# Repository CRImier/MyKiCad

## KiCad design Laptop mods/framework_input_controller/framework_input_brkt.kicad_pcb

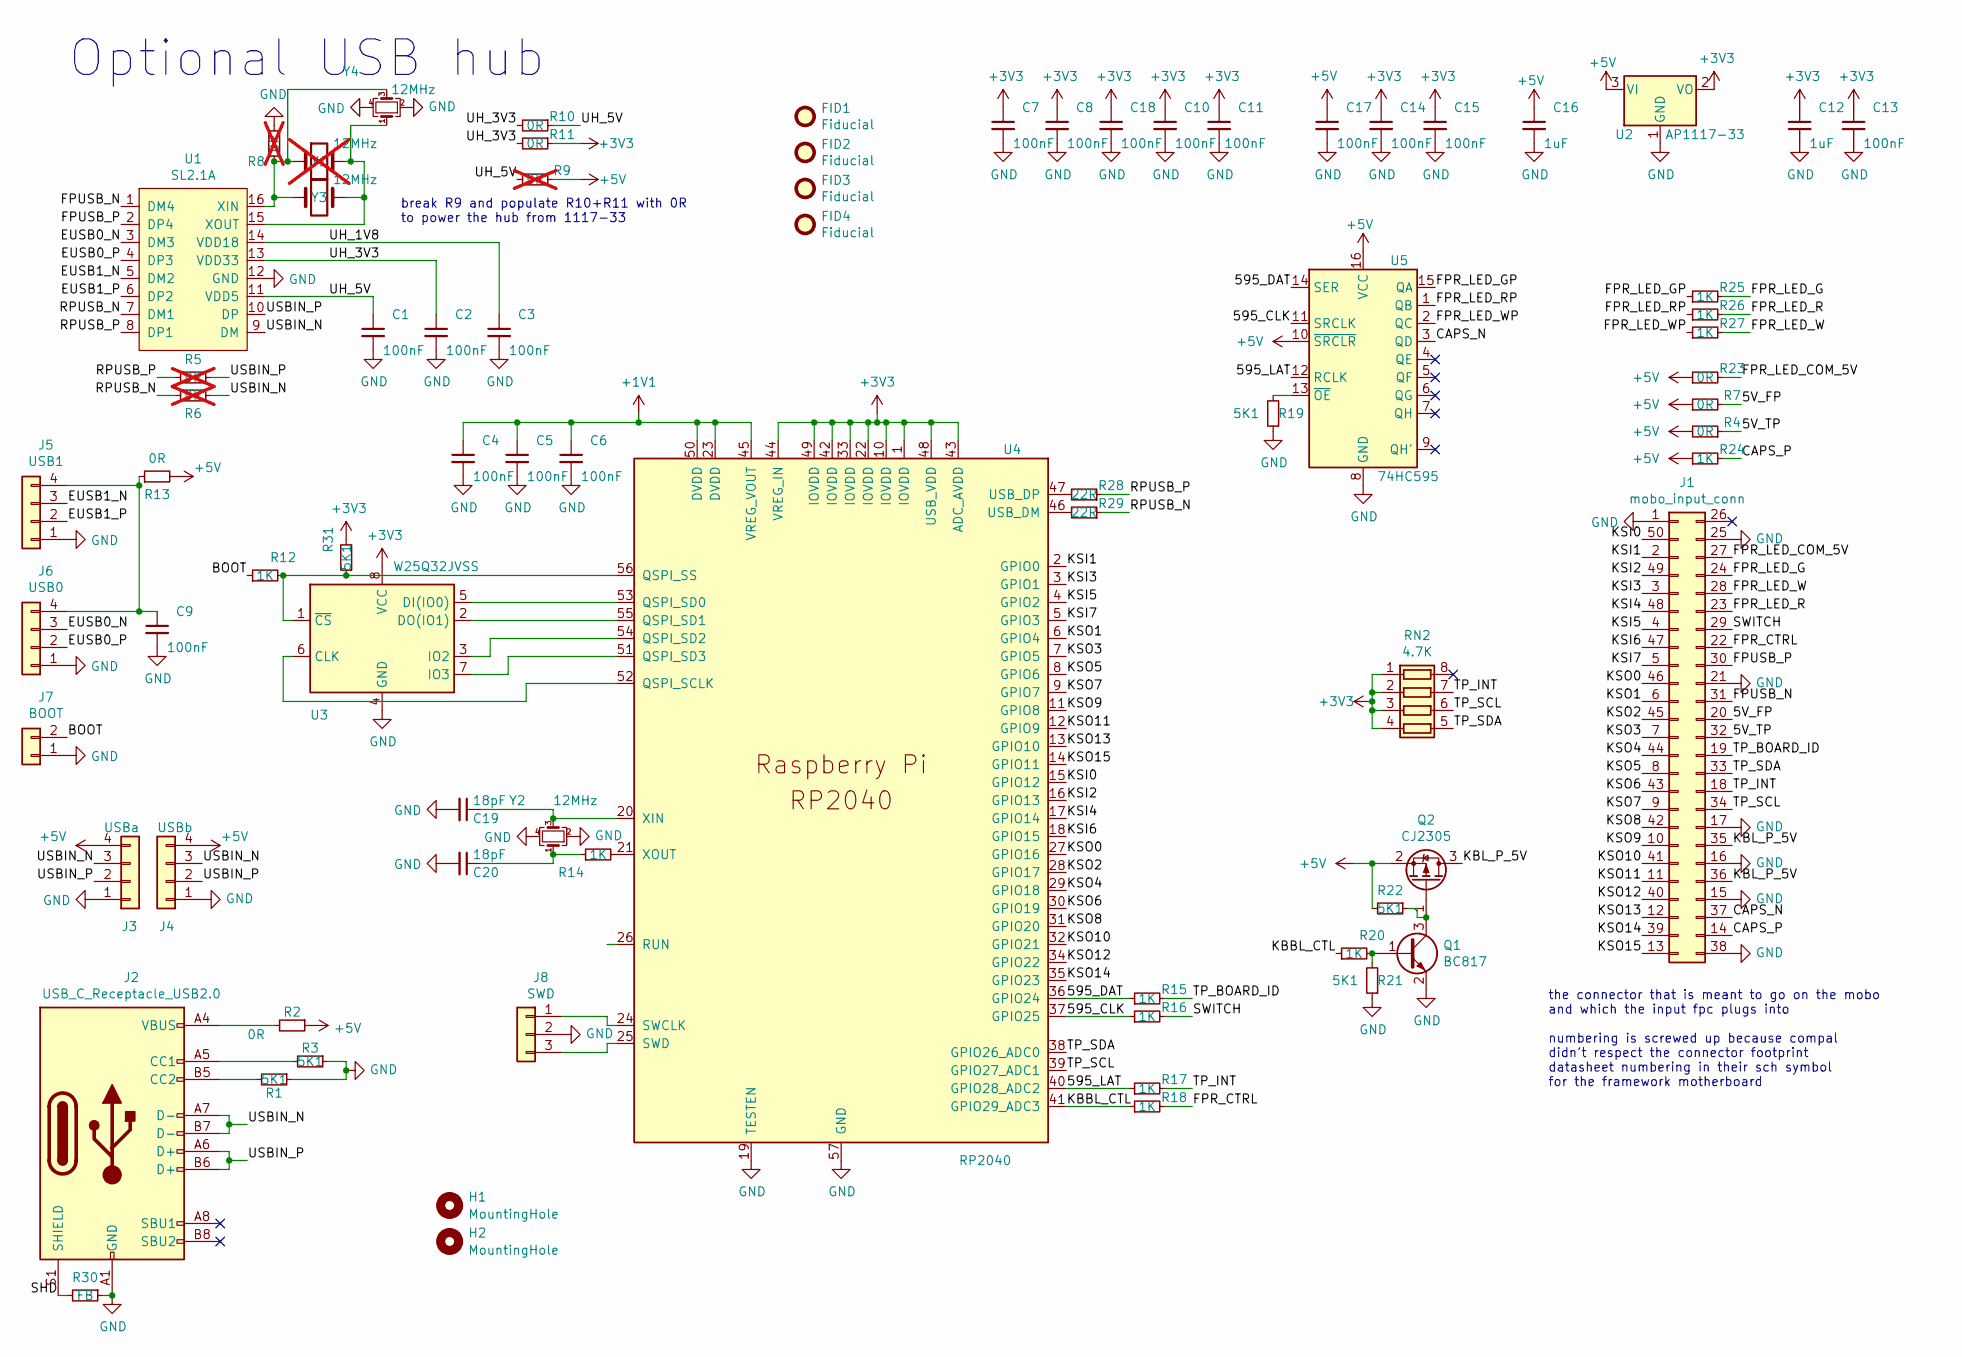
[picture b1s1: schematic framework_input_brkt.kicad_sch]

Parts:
C1, C2, C3, C4, C5, C7, C8, C9, C10, C11, C13, C14, C15, C17, C18: 100nF; C_0603_1608Metric
C6: 100nF; R_0603_1608Metric
C12, C16: 1uF; C_0603_1608Metric
C19, C20: 18pF; C_0603_1608Metric
FID1, FID2, FID3, FID4: Fiducial; Fiducial_1mm_Mask2mm
H1, H2: MountingHole; MountingHole_3mm
J1: mobo_input_conn; Amphenol_10156000
J2: USB_C_Receptacle_USB2.0; USB_C_Receptacle_HRO_TYPE-C-31-M-12
J3: USBa; PinHeader_1x04_P2.54mm_Vertical
J4: USBb; PinHeader_1x04_P2.54mm_Vertical
J5: USB1; PinHeader_1x04_P2.54mm_Vertical
J6: USB0; PinHeader_1x04_P2.54mm_Vertical
J7: BOOT; PinHeader_1x02_P2.54mm_Vertical
J8: SWD; PinHeader_1x03_P2.54mm_Vertical
Q1: BC817; SOT-23
Q2: CJ2305; SOT-23
R1, R3, R19, R21, R22, R31: 5K1; R_0603_1608Metric
R2, R13: 0R; R_0805_2012Metric
R4, R7, R10, R11, R23: 0R; R_0603_1608Metric
R5, R6, R8, R9: 0R; R_0603_1608Metric; not fitted
R12, R14, R15, R16, R17, R18, R20, R24, R25, R26, R27: 1K; R_0603_1608Metric
R28, R29: 22R; R_0402_1005Metric
R30: FB; R_0805_2012Metric
RN2: 4.7K; R_Array_Concave_4x0603
U1: SL2.1A; SO-16_3.9x9.9mm_P1.27mm
U2: AP1117-33; SOT-223-3_TabPin2
U3: W25Q32JVSS; SOIC-8_5.23x5.23mm_P1.27mm
U4: RP2040; RP2040-QFN-56
U5: 74HC595; SO-16_3.9x9.9mm_P1.27mm
Y1: 12MHz; Crystal_HC49-U_Vertical; not fitted
Y2, Y4: 12MHz; Crystal_SMD_3225-4Pin_3.2x2.5mm
Y3: 12MHz; Crystal_SMD_HC49-SD

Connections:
+1V1: C4.1, C5.1, C6.1, U4.23 (DVDD), U4.45 (VREG_VOUT), U4.50 (DVDD)
+3V3: C7.1, C8.1, C10.1, C11.1, C12.1, C13.1, C14.1, C15.1, C18.1, R11.1, R31.2, RN2.1 (R1.1), RN2.2 (R2.1), RN2.3 (R3.1), RN2.4 (R4.1), U2.2 (VO), U3.8 (VCC), U4.1 (IOVDD), U4.10 (IOVDD), U4.22 (IOVDD), U4.33 (IOVDD), U4.42 (IOVDD), U4.43 (ADC_AVDD), U4.44 (VREG_IN), U4.48 (USB_VDD), U4.49 (IOVDD)
+5V: C16.1, C17.1, J3.4, J4.4, Q2.2 (S), R2.1, R4.2, R7.1, R9.1, R13.2, R22.2, R23.1, R24.1, U2.3 (VI), U5.10 (~SRCLR), U5.16 (VCC)
/5V_FP: J1.20, R7.2
/5V_TP: J1.32, R4.1
/595_CLK: R16.1, U4.37 (GPIO25), U5.11 (SRCLK)
/595_DAT: R15.1, U4.36 (GPIO24), U5.14 (SER)
/595_LAT: R17.1, U4.40 (GPIO28_ADC2), U5.12 (RCLK)
/BOOT: J7.2, R12.1
/CAPS_N: J1.37, U5.3 (QD)
/CAPS_P: J1.14, R24.2
/EUSB0_N: J6.3, U1.3 (DM3)
/EUSB0_P: J6.2, U1.4 (DP3)
/EUSB1_N: J5.3, U1.5 (DM2)
/EUSB1_P: J5.2, U1.6 (DP2)
/FPR_CTRL: J1.22, R18.2
/FPR_LED_COM_5V: J1.27, R23.2
/FPR_LED_G: J1.24, R25.2
/FPR_LED_GP: R25.1, U5.15 (QA)
/FPR_LED_R: J1.23, R26.2
/FPR_LED_RP: R26.1, U5.1 (QB)
/FPR_LED_W: J1.28, R27.2
/FPR_LED_WP: R27.1, U5.2 (QC)
/FPUSB_N: J1.31, U1.1 (DM4)
/FPUSB_P: J1.30, U1.2 (DP4)
/KBBL_CTL: R18.1, R20.1, U4.41 (GPIO29_ADC3)
/KBL_P_5V: J1.35, J1.36, Q2.3 (D)
/KSI0: J1.50, U4.15 (GPIO12)
/KSI1: J1.2, U4.2 (GPIO0)
/KSI2: J1.49, U4.16 (GPIO13)
/KSI3: J1.3, U4.3 (GPIO1)
/KSI4: J1.48, U4.17 (GPIO14)
/KSI5: J1.4, U4.4 (GPIO2)
/KSI6: J1.47, U4.18 (GPIO15)
/KSI7: J1.5, U4.5 (GPIO3)
/KSO0: J1.46, U4.27 (GPIO16)
/KSO1: J1.6, U4.6 (GPIO4)
/KSO2: J1.45, U4.28 (GPIO17)
/KSO3: J1.7, U4.7 (GPIO5)
/KSO4: J1.44, U4.29 (GPIO18)
/KSO5: J1.8, U4.8 (GPIO6)
/KSO6: J1.43, U4.30 (GPIO19)
/KSO7: J1.9, U4.9 (GPIO7)
/KSO8: J1.42, U4.31 (GPIO20)
/KSO9: J1.10, U4.11 (GPIO8)
/KSO10: J1.41, U4.32 (GPIO21)
/KSO11: J1.11, U4.12 (GPIO9)
/KSO12: J1.40, U4.34 (GPIO22)
/KSO13: J1.12, U4.13 (GPIO10)
/KSO14: J1.39, U4.35 (GPIO23)
/KSO15: J1.13, U4.14 (GPIO11)
/RPUSB_N: R6.1, R29.1, U1.7 (DM1)
/RPUSB_P: R5.1, R28.1, U1.8 (DP1)
/SHD: J2.S1 (SHIELD), R30.2
/SWITCH: J1.29, R16.2
/TP_BOARD_ID: J1.19, R15.2
/TP_INT: J1.18, R17.2, RN2.7 (R2.2)
/TP_SCL: J1.34, RN2.6 (R3.2), U4.39 (GPIO27_ADC1)
/TP_SDA: J1.33, RN2.5 (R4.2), U4.38 (GPIO26_ADC0)
/UH_1V8: C3.1, U1.14 (VDD18)
/UH_3V3: C2.1, R10.2, R11.2, U1.13 (VDD33)
/UH_5V: C1.1, R9.2, R10.1, U1.11 (VDD5)
/USBIN_N: J2.A7 (D-), J2.B7 (D-), J3.3, J4.3, R6.2, U1.9 (DM)
/USBIN_P: J2.A6 (D+), J2.B6 (D+), J3.2, J4.2, R5.2, U1.10 (DP)
GND: C1.2, C2.2, C3.2, C4.2, C5.2, C6.2, C7.2, C8.2, C9.2, C10.2, C11.2, C12.2, C13.2, C14.2, C15.2, C16.2, C17.2, C18.2, C19.2, C20.2, J1.1, J1.15, J1.16, J1.17, J1.21, J1.25, J1.38, J2.A1 (GND), J2.A12 (GND), J2.B1 (GND), J2.B12 (GND), J3.1, J4.1, J5.1, J6.1, J7.1, J8.2, Q1.2 (E), R1.1, R3.1, R8.2, R19.1, R21.1, R30.1, U1.12 (GND), U2.1 (GND), U3.4 (GND), U4.19 (TESTEN), U4.57 (GND), U5.8 (GND), Y2.2, Y2.4, Y4.2, Y4.4
unnamed: C20.1, R14.1, Y2.1
unnamed: J2.A5 (CC1), R3.2
unnamed: J2.B5 (CC2), R1.2
unnamed: J2.A4 (VBUS), J2.A9 (VBUS), J2.B4 (VBUS), J2.B9 (VBUS), R2.2
unnamed: C9.1, J5.4, J6.4, R13.1
unnamed: J8.1, U4.24 (SWCLK)
unnamed: J8.3, U4.25 (SWD)
unnamed: Q1.1 (B), R20.2, R21.2
unnamed: Q1.3 (C), Q2.1 (G), R22.1
unnamed: R8.1, U1.16 (XIN), Y1.1, Y3.1, Y4.3
unnamed: U1.15 (XOUT), Y1.2, Y3.2, Y4.1
unnamed: U3.6 (CLK), U4.52 (QSPI_SCLK)
unnamed: U3.5 (DI(IO0)), U4.53 (QSPI_SD0)
unnamed: U3.2 (DO(IO1)), U4.55 (QSPI_SD1)
unnamed: U3.3 (IO2), U4.54 (QSPI_SD2)
unnamed: U3.7 (IO3), U4.51 (QSPI_SD3)
unnamed: R12.2, R31.1, U3.1 (~CS), U4.56 (QSPI_SS)
unnamed: R29.2, U4.46 (USB_DM)
unnamed: R28.2, U4.47 (USB_DP)
unnamed: C19.1, U4.20 (XIN), Y2.3
unnamed: R14.2, U4.21 (XOUT)
unnamed: R19.2, U5.13 (~OE)

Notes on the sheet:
Optional USB hub
the connector that is meant to go on the mobo and which the input fpc plugs into numbering is screwed up because compal didn't respect the connector footprint datasheet numbering in their sch symbol for the framework motherboard
break R9 and populate R10+R11 with 0R to power the hub from 1117-33

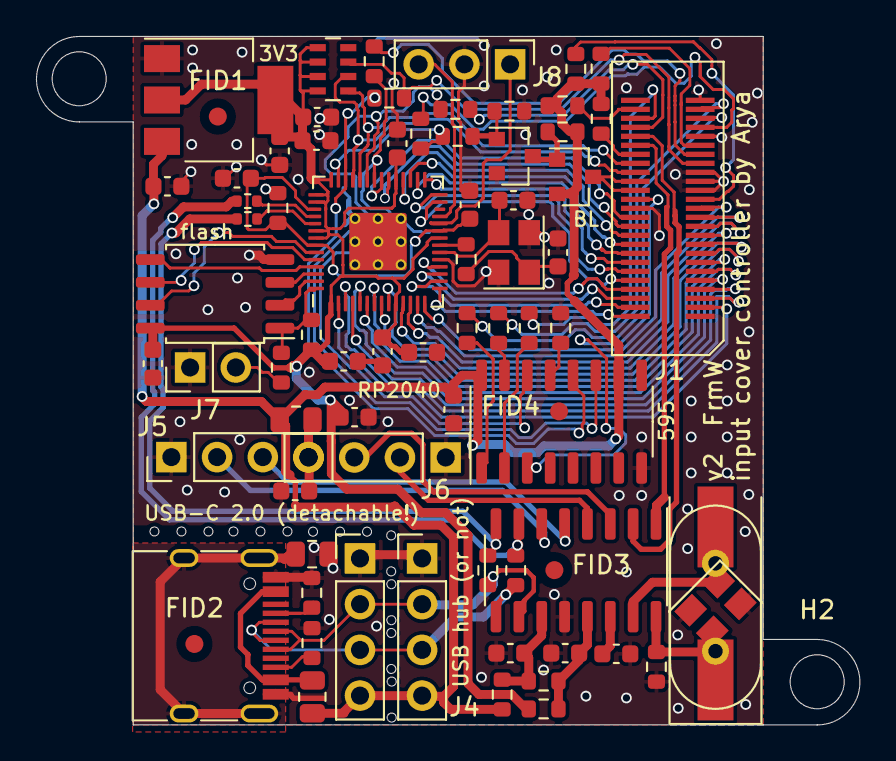
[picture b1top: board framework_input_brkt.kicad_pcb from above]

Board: 2 copper layers, 45.8 x 38.2 mm, 77 parts (0 on the bottom side), 87 nets.

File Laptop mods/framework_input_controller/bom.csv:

Designator,Footprint,Quantity,Value,LCSC Part #
"C1, C10, C11, C13, C14, C15, C17, C18, C2, C3, C4, C5, C6, C7, C8, C9",0603,16,100nF,C14663
"C12, C16",0603,2,1uF,C15849
"C19, C20",0603,2,18pF,C1647
"FID1, FID2, FID3, FID4",Fiducial_1mm_Mask2mm,4,Fiducial,
J1,Amphenol_10156000,1,mobo_input_conn,
J2,USB_C_Receptacle_HRO_TYPE-C-31-M-12,1,USB_C_Receptacle_USB2.0,C2874568
Q1,SOT-23,1,BC817,C2137
Q2,SOT-23,1,CJ2305,C8549
"R1, R19, R21, R22, R3, R31",0603,5,5K1,C23186
"R10, R11, R23, R4, R5, R6, R7, R8, R9",0603,9,0R,C21189
"R12, R14, R15, R16, R17, R18, R20, R24, R25, R26, R27",0603,11,1K,C21190
"R13, R2",0805,2,0R,C17477
R30,0805,1,FB,C1011
"R28, R29",0402,2,22R,C25092
RN2,R_Array_Concave_4x0603,1,4.7K,C1980
U1,SO-16_3.9x9.9mm_P1.27mm,1,SL2.1A,C192893
U2,SOT-223-3_TabPin2,1,AP1117-33,C5400
U3,SOIC-8_5.23x5.23mm_P1.27mm,1,W25Q32JVSS,C179173
U4,RP2040-QFN-56,1,RP2040,C2040
U5,SO-16_3.9x9.9mm_P1.27mm,1,74HC595,C2927048
Y1,Crystal_HC49-U_Vertical,1,12MHz,
Y2,Crystal_SMD_3225-4Pin_3.2x2.5mm,1,12MHz,C258938
Y3,Crystal_SMD_HC49-SD,1,12MHz,C108151

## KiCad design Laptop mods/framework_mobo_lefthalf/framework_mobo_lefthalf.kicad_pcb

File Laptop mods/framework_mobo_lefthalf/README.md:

# Framework Display Shim

This is a start for reimplementing the Framework Mainboard.
Currently, this board is a USB-C DP altmode to Framework display adapter,
using the same connector and pinout that the Framework mainboard uses.

This adapter is currently going through the testing process, with a number of fundamental fixes scheduled for the v3 version.

## Images

## Notes

- This board is untested and there's no guarantees of fitness.
- I recommend a stencil for assembling this board.

## Info

- Software: Kicad 7
- Version: 2
- PCB size: w*h
- Layer count: 6
- Recommended thickness: 0.8mm/1mm (needs to match Framework mainboard thickness)

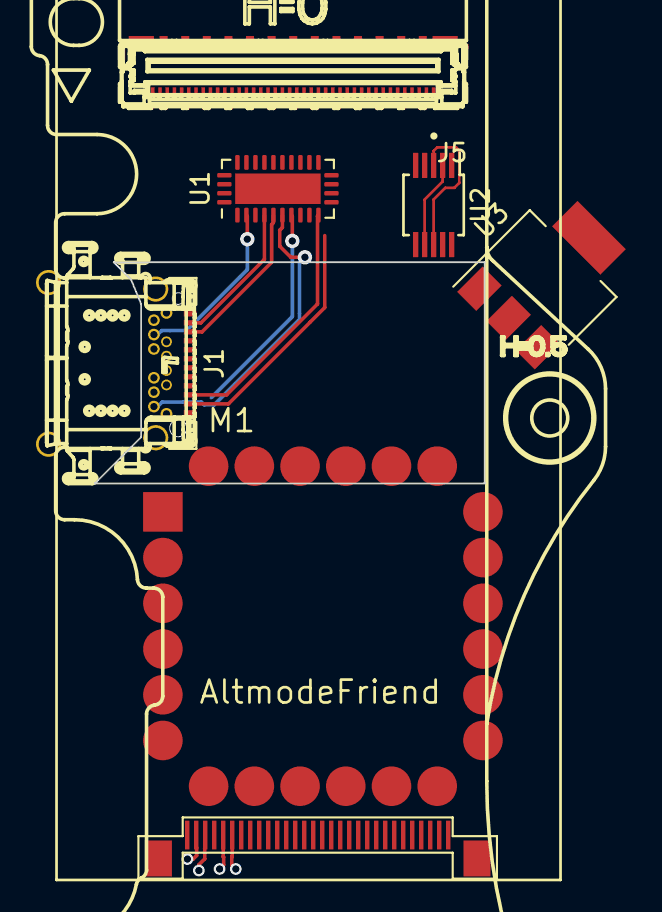
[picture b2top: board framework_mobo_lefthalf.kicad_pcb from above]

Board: 6 copper layers, 7 parts (0 on the bottom side), 39 nets.

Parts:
J1: USB_C_Receptacle; USB_C_Receptacle_Amphenol_12401548E4-2A_CircularHoles
J2: IF; FPC_30
J5: Display; IPEX_20879-040E-01
M1: AltmodeFriend; altmode_friend
U1: VL170; QFN-28-1EP_3x6mm_P0.5mm_EP1.7x4.75mm
U2: FSUSB30MUX; MSOP-10_3x3mm_P0.5mm
U3: AP1117-33; SOT-223-3_TabPin2

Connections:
3V_TS: J5.29, J5.30
+3.3V: J2.13, J2.14, J2.15, M1.8 (3V3), U3.2 (VO)
+3.3VP: U1.22 (VCC), U2.10 (VCC)
/3VP_CTL: J2.9, M1.13 (GP7)
/CC1: J1.A5 (CC1), M1.20 (CC1)
/CC2: J1.B5 (CC2), M1.22 (CC2)
/PD_D+: J2.3, M1.24 (D+)
/PD_D-: J2.2, M1.23 (D-)
/PD_UART_RX: J2.12, M1.5 (GP1)
/PD_UART_TX: J2.11, M1.4 (GP0)
/SBU_OE: M1.11 (GP5), U2.9 (~OE)
/SBU_S: M1.12 (GP6), U2.1 (S)
/TC1_CSBU1: J1.A8 (SBU1), U1.11 (CSBU1)
/TC1_CSBU2: J1.B8 (SBU2), U1.12 (CSBU2)
/TC1_RX1+: J1.B11 (RX1+), U1.1 (RX1_P)
/TC1_RX1-: J1.B10 (RX1-), U1.2 (RX1_N)
/TC1_RX2+: J1.A11 (RX2+), U1.9 (RX2_P)
/TC1_RX2-: J1.A10 (RX2-), U1.10 (RX2_N)
/TC1_SBU1: U1.13 (SBU1), U2.4 (D+)
/TC1_SBU2: U1.14 (SBU2), U2.6 (D-)
/TC1_TX1+: J1.A2 (TX1+), U1.4 (TX1_P)
/TC1_TX1-: J1.A3 (TX1-), U1.5 (TX1_N)
/TC1_TX2+: J1.B2 (TX2+), U1.6 (TX2_P)
/TC1_TX2-: J1.B3 (TX2-), U1.7 (TX2_N)
/TC_D+: J1.A6 (D+), J1.B6 (D+), J2.6
/TC_D-: J1.A7 (D-), J1.B7 (D-), J2.5
/VL170_AMSEL: M1.7 (GP3), U1.8 (AMSEL)
/VL170_EN: M1.6 (GP2), U1.17 (EN)
/VL170_POL: M1.10 (GP4), U1.3 (POL)
AUX+: U2.3 (HSD2+), U2.8 (HSD1-)
AUX-: U2.2 (HSD1+), U2.7 (HSD2-)
BLK_OFF_N: J5.23, M1.16 (GP10)
BLK_PWM_LCD: J5.22, M1.17 (GP15)
BL_POWER: J5.1, J5.2, J5.3
BL_PWR_IN: J2.18, J2.19
DPHPD: J5.21, M1.18 (GP17)
GND: J1.A1 (GND), J1.A12 (GND), J1.B1 (GND), J1.B12 (GND), J1.S1 (SHIELD), J2.1, J2.4, J2.7, J2.10, J2.16, J2.17, J2.20, J2.21, J2.22, J2.23, J2.24, J2.MP (MountPin), J5.5, J5.8, J5.11, J5.14, J5.17, J5.20, J5.39, J5.40, M1.9 (GND), M1.19 (GND), U1.29 (GND), U2.5 (GND), U3.1 (GND)
unnamed: J5.26, J5.27, J5.28
VBUS: J1.A4 (VBUS), J1.A9 (VBUS), J1.B4 (VBUS), J1.B9 (VBUS), J2.25, J2.26, J2.27, J2.28, J2.29, J2.30, U3.3 (VI)

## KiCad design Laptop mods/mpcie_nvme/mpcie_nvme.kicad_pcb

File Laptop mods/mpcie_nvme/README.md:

# mPCIe-NVMe adapter

This is an adapter to easily connect NVMe drives to systems with
mPCIe slots. It will support M.2 M-key and M+B-key drives.
It's a half-height card, if you'd like to put it in a full-height slot,
you'll need a mechanical adapter of some kind.

There are traces with mask openings near the mPCIe card edge that allow you
to tap into any of the mPCIe socket pins connected to the card's pads (except the PCI-E pins).
Use them wisely!

This board is untested and there's no guarantees of fitness.

- PCB size: 30x26.8mm
- Layer count: 2
- Recommended thickness: 1mm (won't fit in an mPCIe slot otherwise)

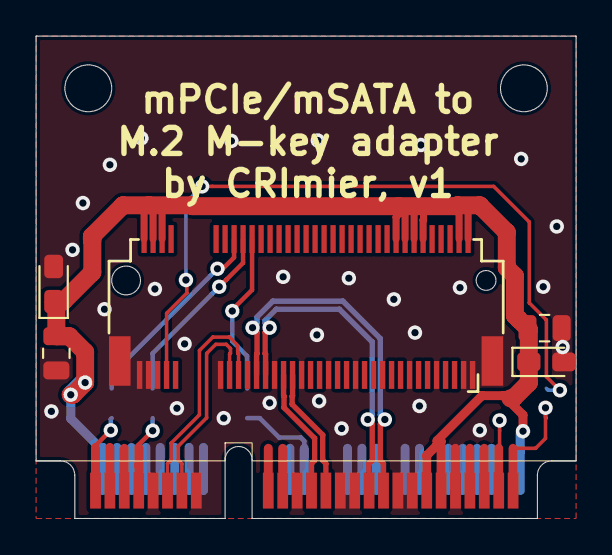
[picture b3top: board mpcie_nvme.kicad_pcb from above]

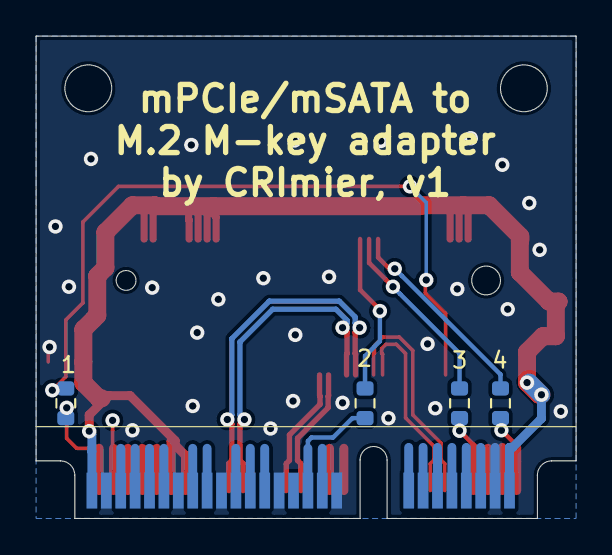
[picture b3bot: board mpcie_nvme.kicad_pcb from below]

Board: 2 copper layers, 30.0 x 26.8 mm, 10 parts (4 on the bottom side), 16 nets.

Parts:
C1, C3: 100nF; C_0805_2012Metric
C2, C4: 100uF; CP_EIA-2012-12_Kemet-R_Pad1.30x1.05mm_HandSolder
R1, R2, R3, R5: 0R; R_0603_1608Metric
U1: MPCIE-Socket; mpcie-half-card
U2: NGFF_M; Conn_TE-M.2-0.5-67P-doublesided_TypeM

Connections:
+3V3: C1.1, C2.1, C3.1, C4.1, U1.2, U1.24, U1.39, U1.41, U1.52, U2.2, U2.4, U2.12, U2.14, U2.16, U2.18, U2.70, U2.72, U2.74
DET: R5.1, U2.69
GND: C1.2, C2.2, C3.2, C4.2, U1.4, U1.9, U1.15, U1.18, U1.21, U1.26, U1.27, U1.29, U1.34, U1.35, U1.37, U1.40, U1.43, U1.50, U2.1, U2.3, U2.9, U2.15, U2.21, U2.27, U2.33, U2.39, U2.45, U2.51, U2.57, U2.71, U2.73, U2.75, U2.MP
unnamed: R1.1, U1.22
unnamed: R2.2, U1.1
unnamed: R3.2, U1.7
unnamed: R5.2, U1.51
P0_RX+: U1.25, U2.41
P0_RX-: U1.23, U2.43
P0_TX+: U1.31, U2.47
P0_TX-: U1.33, U2.49
PCLK+: U1.13, U2.55
PCLK-: U1.11, U2.53
PERST: R1.2, U2.50
~CLKREQ: R3.1, U2.52
~WAKE: R2.1, U2.54

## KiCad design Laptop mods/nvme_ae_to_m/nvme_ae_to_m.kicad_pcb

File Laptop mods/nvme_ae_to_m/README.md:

# M.2 A+E to M key adapter

This board allows you to insert M-key M.2 SSDs into A/E-key slots.
It should support NVMe SSDs at 1x speed. It might even support SATA if the PCI-E lane
going to the slot is PCI-E/SATA and you can figure out a way to switch it
into SATA mode, but that doesn't happen all that often.

M.2 socket position is calculated so that the board
mechanically converts a 2230 card into a 2242 card - that's not terribly useful
since most WiFi cards I see are 2230 already, I just didn't see any sense
in changing the position. The board itself is 2230.
FOXCONN AS0BC21-S20BM-7H socket datasheet was used for reference.

This board also breaks out A+E slot USB 2.0 signals, 3.3V and GND
on a separate 4-pin 2mm pin header. It's mostly intended for you
to solder wires to. Draw 3.3V from there at your own peril.

There are resistors on the bottom for interrupting PCI-E&other control signals
if any of them interfere with operation of your SSD:

* 1 interrupts PERST
* 2 interrupts CLKREQ
* 3 interrupts PEWAKE
* 4 interrupts SUSCLK

There are also traces with mask openings near the card edge that allow you
to tap into any of the M.2 socket pins connected to the A+E pads. Use them wisely!

USB header pinout is silkscreened on the board's bottom layer.

Changes in v2:

- Removed capacitors
- v1 had TX and RX pairs swapped, fixed in new revision

- Software: Kicad 6
- Version: 2
- PCB size: 22*16,42
- Layer count: 2
- Recommended thickness: 0.8mm (M.2 card thickness)

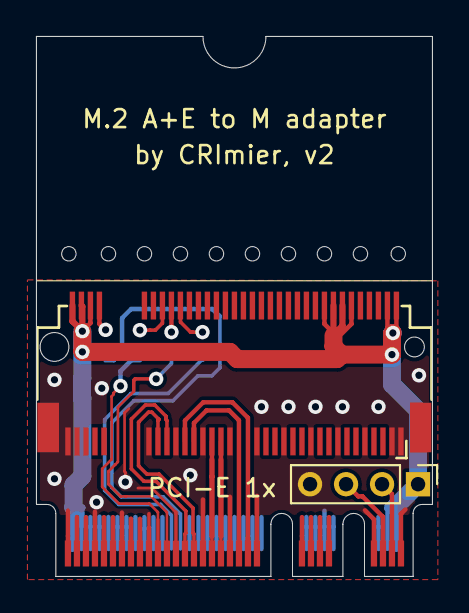
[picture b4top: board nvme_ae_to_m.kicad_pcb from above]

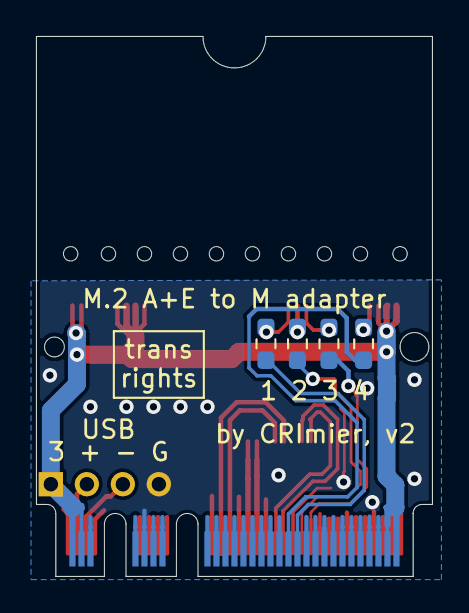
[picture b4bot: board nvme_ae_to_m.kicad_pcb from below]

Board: 2 copper layers, 22.0 x 30.0 mm, 7 parts (4 on the bottom side), 18 nets.

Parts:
J1: USB; PinHeader_1x04_P2.00mm_Vertical
R1, R2, R3, R4: 0R; R_0603_1608Metric_Pad0.98x0.95mm_HandSolder
U1: NGFF_M; Conn_TE-M.2-0.5-67P-doublesided_TypeM
U2: NGFF_AE; NGFF_A+E

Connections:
+3V3: J1.1, U1.2, U1.4, U1.12, U1.14, U1.16, U1.18, U1.70, U1.72, U1.74, U2.2, U2.4, U2.72, U2.74
/PER0+: U1.49, U2.35
/PER0-: U1.47, U2.37
/PET0+: U1.41, U2.41
/PET0-: U1.43, U2.43
/REFCLK+: U1.55, U2.47
/REFCLK-: U1.53, U2.49
D+: J1.2, U2.3
D-: J1.3, U2.5
GND: J1.4, U1.1, U1.3, U1.9, U1.15, U1.21, U1.27, U1.33, U1.39, U1.45, U1.51, U1.57, U1.71, U1.73, U1.75, U1.MP, U2.1, U2.7, U2.18, U2.33, U2.39, U2.45, U2.51, U2.57, U2.63, U2.69, U2.75
unnamed: R1.1, U2.53
unnamed: R2.1, U2.55
unnamed: R3.2, U2.52
unnamed: R4.2, U2.50
SUSCLK: R4.1, U1.68
~CLKREQ: R1.2, U1.52
~PERST: R3.1, U1.50
~PEWAKE: R2.2, U1.54

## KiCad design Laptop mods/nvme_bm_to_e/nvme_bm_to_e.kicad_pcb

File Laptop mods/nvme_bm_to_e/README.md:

# M.2 B+M to E key adapter

This board allows you to insert E-key or A+E-key WiFi cards into B-key or M-key slots.
It should support PCIe WiFi cards and passes the USB channel through.
It won't support CNVi cards.

M.2 socket position is calculated so that the board
mechanically converts a 2230 card into a 2242 card -
which is perfect for WiFi cards in 2242-oriented B-key slots.
FOXCONN AS0BC21-S20BM-7H socket datasheet was used for reference.

This board also breaks out USB 2.0 signals and GND
on a separate 4-pin 2mm pin header. It's mostly intended for you
to solder wires to, in case you're 
If inserting into M.2 socket, you might have to mask USB pins on the card edge side
with kapton tape.

There are resistors on the bottom for interrupting PCI-E&other control signals
if any of them interfere with operation of your WiFi card:

* 1 interrupts SUSCLK
* 2 connects B-key W_DISABLE to E-key W_DIS2
* 3 connects B-key W_DISABLE to E-key W_DIS1
* 4 interrupts PERST
* 5 interrupts PEWAKE
* 6 interrupts CLKREQ

You can snap part of this board off if you need to save space.
There are also traces with mask openings near the card edge that allow you
to tap into any of the M.2 socket pins connected to the B+M pads. Use them wisely!

USB header pinout is silkscreened on the board's bottom layer.
This board is untested and there's no guarantees of fitness.

- PCB size: 22*42mm
- Layer count: 2
- Recommended thickness: 0.8mm (M.2 card thickness)

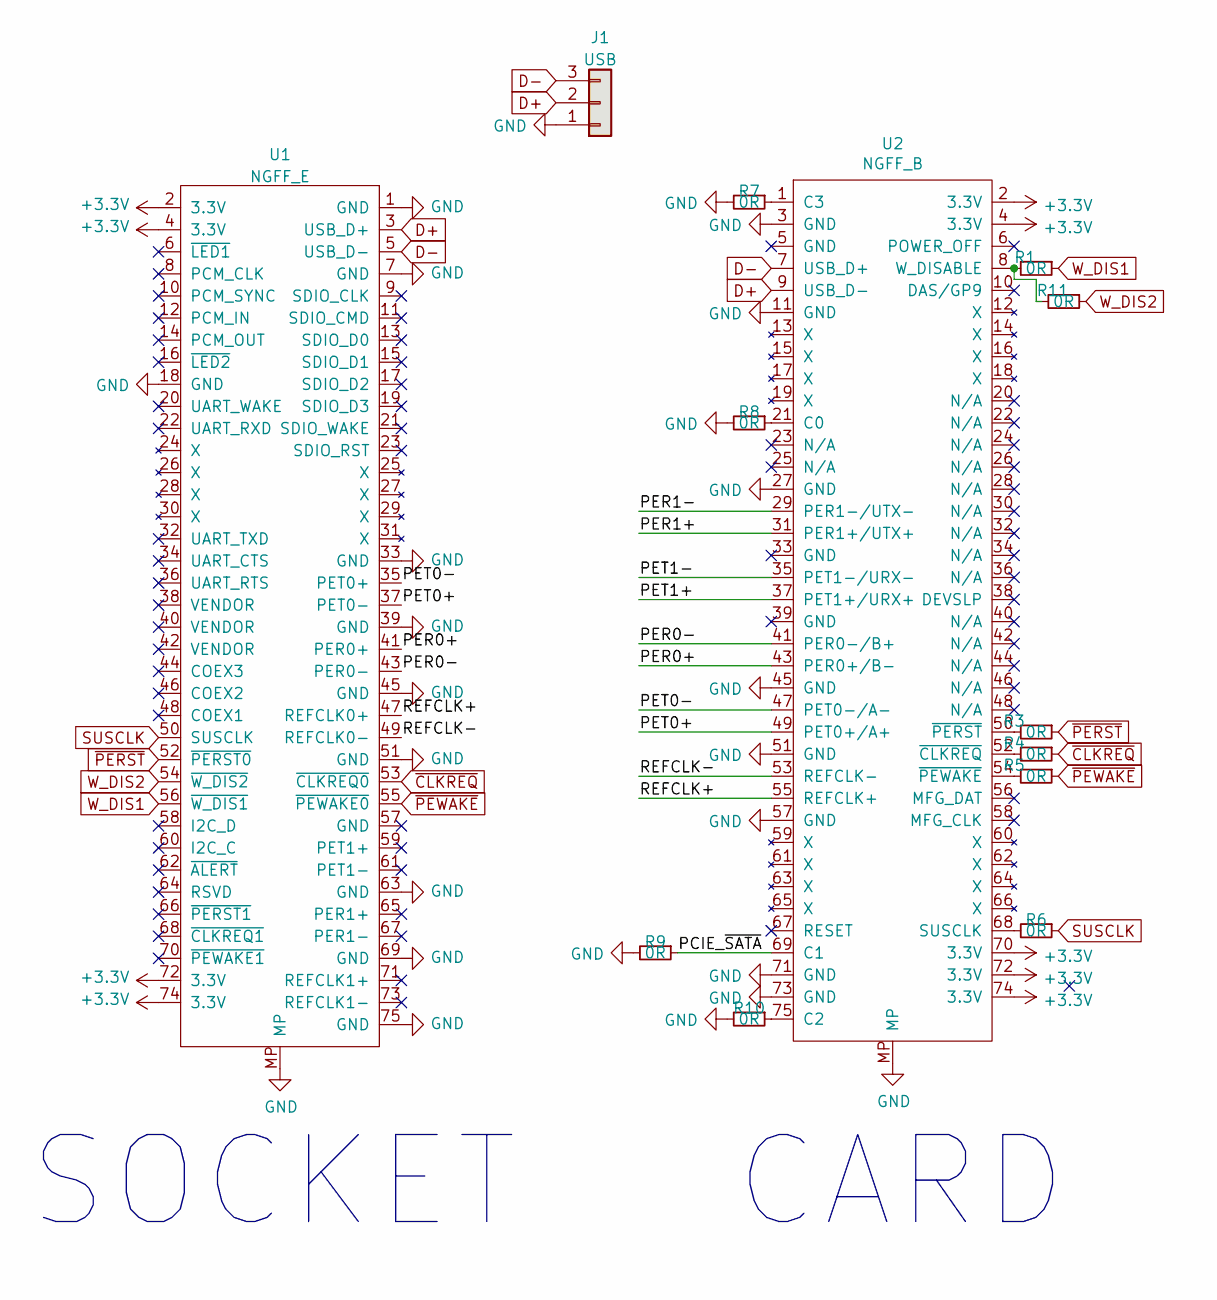
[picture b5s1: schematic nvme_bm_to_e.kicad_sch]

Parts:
J1: USB; PinHeader_1x03_P2.00mm_Vertical
R1, R3, R4, R5, R6, R7, R8, R9, R10, R11: 0R; R_0402_1005Metric
U1: NGFF_E; Conn_TE-M.2-0.5-67P-doublesided_TypeE
U2: NGFF_B; NGFF_B+M

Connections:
+3V3: U1.2 (3.3V), U1.4 (3.3V), U1.72 (3.3V), U1.74 (3.3V), U2.2 (3.3V), U2.4 (3.3V), U2.70 (3.3V), U2.72 (3.3V), U2.74 (3.3V)
/PCIE_~SATA: R9.1, U2.69 (C1)
/PER0+: U1.41 (PER0+), U2.43 (PER0+/B-)
/PER0-: U1.43 (PER0-), U2.41 (PER0-/B+)
/PER1+: U2.31 (PER1+/UTX+)
/PER1-: U2.29 (PER1-/UTX-)
/PET0+: U1.37 (PET0-), U2.49 (PET0+/A+)
/PET0-: U1.35 (PET0+), U2.47 (PET0-/A-)
/PET1+: U2.37 (PET1+/URX+)
/PET1-: U2.35 (PET1-/URX-)
/REFCLK+: U1.47 (REFCLK0+), U2.55 (REFCLK+)
/REFCLK-: U1.49 (REFCLK0-), U2.53 (REFCLK-)
D+: J1.2, U1.3 (USB_D+), U2.9 (USB_D-)
D-: J1.3, U1.5 (USB_D-), U2.7 (USB_D+)
GND: J1.1, R7.2, R8.2, R9.2, R10.2, U1.1 (GND), U1.7 (GND), U1.18 (GND), U1.33 (GND), U1.39 (GND), U1.45 (GND), U1.51 (GND), U1.63 (GND), U1.69 (GND), U1.75 (GND), U1.MP, U2.3 (GND), U2.11 (GND), U2.27 (GND), U2.45 (GND), U2.51 (GND), U2.57 (GND), U2.71 (GND), U2.73 (GND), U2.MP
unnamed: R3.2, U2.50 (~PERST)
unnamed: R4.2, U2.52 (~CLKREQ)
unnamed: R5.2, U2.54 (~PEWAKE)
unnamed: R6.2, U2.68 (SUSCLK)
unnamed: R7.1, U2.1 (C3)
unnamed: R8.1, U2.21 (C0)
unnamed: R10.1, U2.75 (C2)
unnamed: R1.2, R11.2, U2.8 (W_DISABLE)
SUSCLK: R6.1, U1.50 (SUSCLK)
W_DIS1: R1.1, U1.56 (~W_DIS1)
W_DIS2: R11.1, U1.54 (~W_DIS2)
~CLKREQ: R4.1, U1.53 (~CLKREQ0)
~PERST: R3.1, U1.52 (~PERST0)
~PEWAKE: R5.1, U1.55 (~PEWAKE0)

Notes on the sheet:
CARD
SOCKET

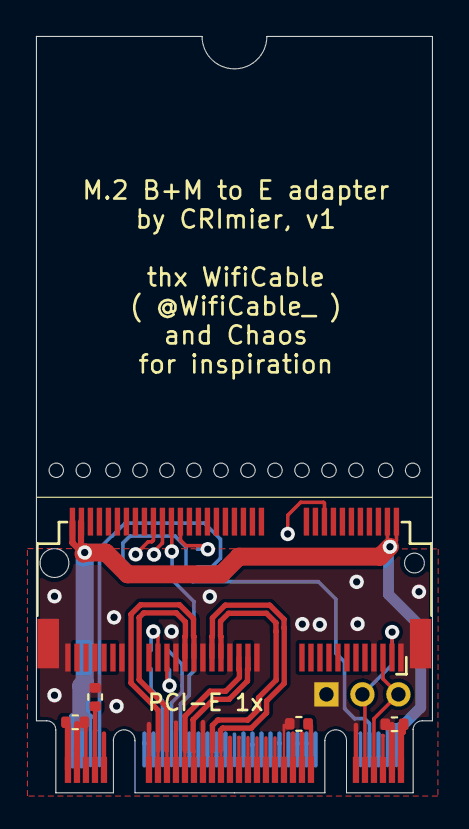
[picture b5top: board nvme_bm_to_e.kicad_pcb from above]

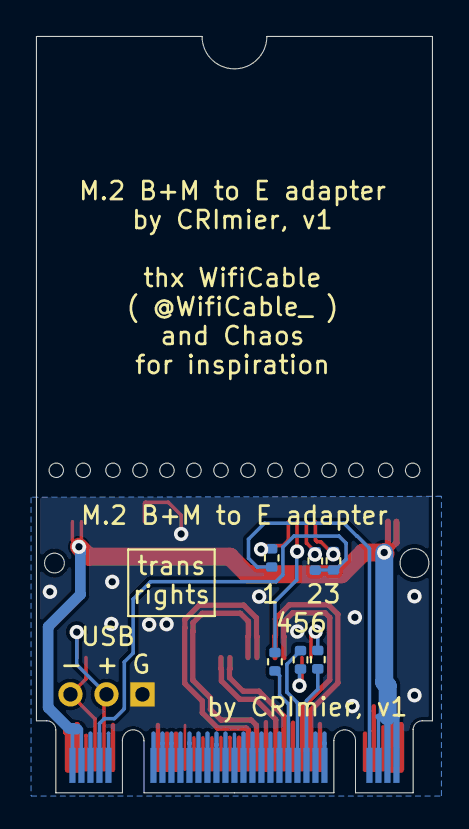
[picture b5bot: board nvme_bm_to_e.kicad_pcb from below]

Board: 2 copper layers, 22.0 x 42.0 mm, 13 parts (6 on the bottom side), 25 nets.

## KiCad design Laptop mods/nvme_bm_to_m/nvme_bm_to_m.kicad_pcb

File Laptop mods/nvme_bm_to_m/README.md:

# M.2 B+M to M key adapter

This board allows you to insert M-key M.2 SSDs into B-key slots.
It should support both SATA and NVMe SSDs, as long as they're supported
by the host machine. This helps if you don't want to cut a B notch
in your M-key SSD to make it fit in your B-key machine.

M.2 socket position is calculated so that the board
mechanically converts a 2230 card into a 2242 card.
FOXCONN AS0BC21-S20BM-7H socket datasheet was used for reference.
So, this board isn't extended to have a mounting hole,
you're supposed to use your SSD's mounting hole instead.

This board forwards a PCIe 2x link, as well as the PCIe/SATA
config pin (pin 69 (nice)).
This board also breaks out B slot USB 2.0 signals, 3.3V and GND
on a separate 4-pin 2mm pin header. It's mostly intended for you
to solder wires to. Draw 3.3V from there at your own peril.

There are resistors on the bottom for interrupting PCI-E&other control signals
if any of them interfere with operation of your SSD:

* 1 interrupts DAA/DSS
* 2 interrupts DEVSLP
* 3 interrupts PERST
* 4 interrupts CLKREQ
* 5 interrupts PEWAKE
* 6 interrupts SUSCLK

There are also traces with mask openings near the card edge that allow you
to tap into any of the M.2 socket pins connected to the B+M pads. Use them wisely!

Updates in v2:

- Removed an ambiguous pin, 5, that isn't GND in both B and M slots
- Removed capacitor footprints
- Changed the board outline for meme purposes

- USB header pinout is silkscreened on the board's bottom layer.
- I recommend a stencil for assembling this board.

- Software: Kicad 6
- Version: 2
- PCB size: 22*42mm
- Layer count: 2
- Recommended thickness: 0.8mm (M.2 card thickness)

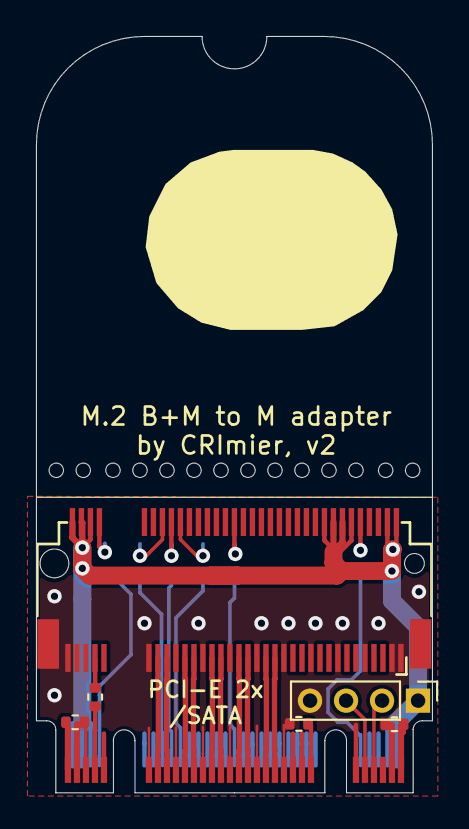
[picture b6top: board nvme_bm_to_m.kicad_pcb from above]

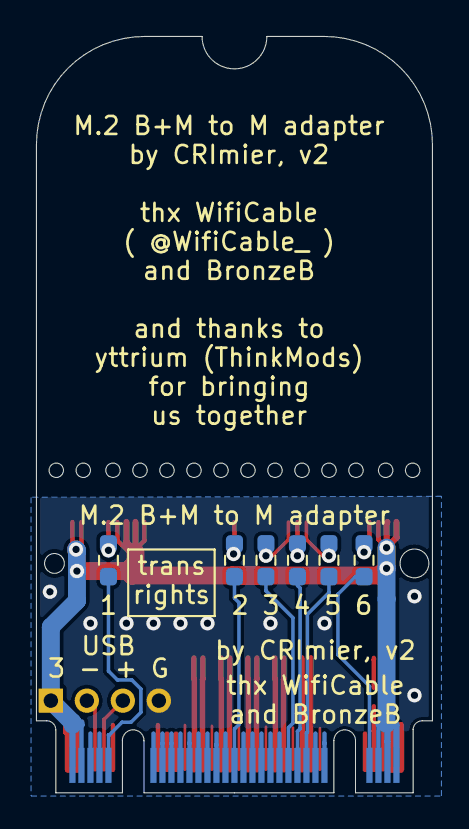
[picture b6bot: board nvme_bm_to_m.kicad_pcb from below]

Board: 2 copper layers, 22.0 x 42.0 mm, 13 parts (6 on the bottom side), 31 nets.

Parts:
J1: USB; PinHeader_1x04_P2.00mm_Vertical
R1, R2, R3, R4, R5, R6: 0R; R_0603_1608Metric_Pad0.98x0.95mm_HandSolder
R7, R8, R9, R10: 0R; R_0402_1005Metric
U1: NGFF_M; Conn_TE-M.2-0.5-67P-doublesided_TypeM
U2: NGFF_B; NGFF_B+M

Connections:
+3V3: J1.1, U1.2 (3.3V), U1.4 (3.3V), U1.12 (3.3V), U1.14 (3.3V), U1.16 (3.3V), U1.18 (3.3V), U1.70 (3.3V), U1.72 (3.3V), U1.74 (3.3V), U2.2 (3.3V), U2.4 (3.3V), U2.70 (3.3V), U2.72 (3.3V), U2.74 (3.3V)
/PCIE_~SATA: R9.2, U1.69 (C1)
/PER0+: U1.43 (PER0+/B-), U2.43 (PER0+/B-)
/PER0-: U1.41 (PER0-/B+), U2.41 (PER0-/B+)
/PER1+: U1.31 (PER1+), U2.31 (PER1+/UTX+)
/PER1-: U1.29 (PER1-), U2.29 (PER1-/UTX-)
/PET0+: U1.49 (PET0+/A+), U2.49 (PET0+/A+)
/PET0-: U1.47 (PET0-/A-), U2.47 (PET0-/A-)
/PET1+: U1.37 (PET1+), U2.37 (PET1+/URX+)
/PET1-: U1.35 (PET1-), U2.35 (PET1-/URX-)
/REFCLK+: U1.55 (REFCLK+), U2.55 (REFCLK+)
/REFCLK-: U1.53 (REFCLK-), U2.53 (REFCLK-)
D+: J1.3, U2.9 (USB_D-)
D-: J1.2, U2.7 (USB_D+)
DAS\DSS: R1.1, U1.10 (DAS/DSS)
DEVSLP: R2.1, U1.38 (DEVSLP)
GND: J1.4, R7.2, R8.2, R10.2, U1.1 (C3), U1.3 (GND), U1.9 (GND), U1.15 (GND), U1.21 (C0), U1.27 (GND), U1.33 (GND), U1.39 (GND), U1.45 (GND), U1.51 (GND), U1.57 (GND), U1.71 (GND), U1.73 (GND), U1.75 (C2), U1.MP, U2.3 (GND), U2.11 (GND), U2.27 (GND), U2.33 (GND), U2.39 (GND), U2.45 (GND), U2.51 (GND), U2.57 (GND), U2.71 (GND), U2.73 (GND)
unnamed: R1.2, U2.10 (DAS/GP9)
unnamed: R2.2, U2.38 (DEVSLP)
unnamed: R3.2, U2.50 (~PERST)
unnamed: R4.2, U2.52 (~CLKREQ)
unnamed: R5.2, U2.54 (~PEWAKE)
unnamed: R6.2, U2.68 (SUSCLK)
unnamed: R7.1, U2.1 (C3)
unnamed: R8.1, U2.21 (C0)
unnamed: R9.1, U2.69 (C1)
unnamed: R10.1, U2.75 (C2)
SUSCLK: R6.1, U1.68 (SUSCLK)
~CLKREQ: R4.1, U1.52 (~CLKREQ)
~PERST: R3.1, U1.50 (~PERST)
~PEWAKE: R5.1, U1.54 (~PEWAKE)

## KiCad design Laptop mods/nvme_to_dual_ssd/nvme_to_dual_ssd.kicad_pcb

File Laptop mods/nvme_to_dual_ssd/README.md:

# M.2 NVMe to dual SSD adapter

This is an adapter board to put two SSDs in a M.2 slot that only accepts one.
It relies on the motherboard having an exposed SATA connection somewhere -
if you have a PCI-E/SATA M.2 slot, oftentimes, there's a Pericom-made (or similar) mux
that switches either PCI-E or SATA to your M.2 slot,
and often you can steal SATA from that while the SSD inserted is in PCI-E x4 mode.

So, to this adapter, you only need to solder or otherwise somehow connect a SATA link to the PCB,
and it'll help you with all the other implications of having a M.2 slot - power,
control signals and the SSD's physical placement.

This board has no decoupling capacitors, and you're on your own when it comes to managing 3.3V power draw
of two SSDs in a slot designed to power one. There seems to be enough 3.3V pins in an M-key slot for two SSDs,
conceptually (each M.2 pin is 0.5A max, 9x0.5A = 4.5A), and I've gone through laptop schematics available to
see the power draw requirements. Turns out that M.2 SSDs are typically connected to the main 3.3V power rail
of the laptop, which typically has quite a bit of power to spare.
I give you no guarantees that it works out for you power-wise, but I'm optimistic.

Also, if you're tapping a Pericom mux and chipset disables the SATA signal when it detects a PCI-E SSD, I can't help you with 
that either. You can sometimes steal a SATA signal from some other place on the board, or maybe even embed a USB-SATA 
converter inside your laptop ;-P

There are resistors on the bottom for interrupting PCI-E&other control signals
if any of them interfere with operation of your SSD, as unlikely as it is:

* 1 interrupts DAA/DSS
* 2 interrupts DEVSLP
* 3 interrupts PERST (PCI-E only)
* 4 interrupts CLKREQ (PCI-E only)
* 5 interrupts PEWAKE (PCI-E only)
* 6 interrupts SUSCLK

SATA signal names are silkscreened on the board's bottom layer.
This board is untested and there's no guarantees of fitness.

- PCB size: 22x80mm
- Layer count: 2
- Recommended thickness: 0.8mm (it's an M.2 card, it has to be 0.8mm)

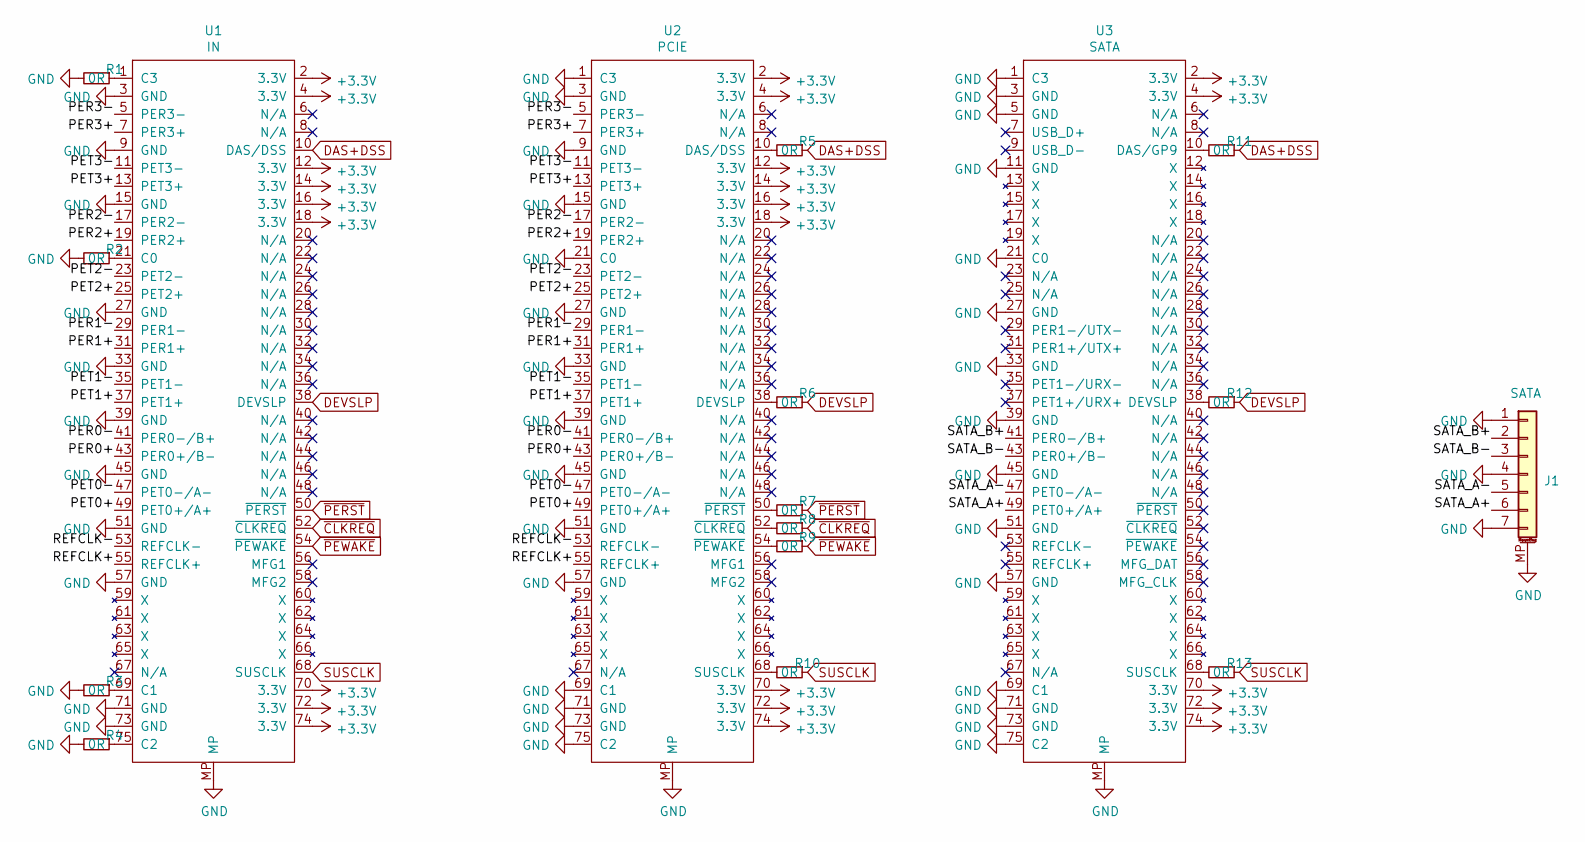
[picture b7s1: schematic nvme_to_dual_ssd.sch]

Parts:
J1: SATA; SATA_SMD
R1, R2, R3, R4, R5, R6, R7, R8, R9, R10, R11, R12, R13: 0R; R_0402_1005Metric
U1: IN; NGFF_M
U2: PCIE; Conn_TE-M.2-0.5-67P-doublesided_TypeM
U3: SATA; Conn_TE-M.2-0.5-67P-doublesided_TypeB

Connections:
+3V3: U1.2 (3.3V), U1.4 (3.3V), U1.12 (3.3V), U1.14 (3.3V), U1.16 (3.3V), U1.18 (3.3V), U1.70 (3.3V), U1.72 (3.3V), U1.74 (3.3V), U2.2 (3.3V), U2.4 (3.3V), U2.12 (3.3V), U2.14 (3.3V), U2.16 (3.3V), U2.18 (3.3V), U2.70 (3.3V), U2.72 (3.3V), U2.74 (3.3V), U3.2 (3.3V), U3.4 (3.3V), U3.70 (3.3V), U3.72 (3.3V), U3.74 (3.3V)
/PER0+: U1.43 (PER0+/B-), U2.43 (PER0+/B-)
/PER0-: U1.41 (PER0-/B+), U2.41 (PER0-/B+)
/PER1+: U1.31 (PER1+), U2.31 (PER1+)
/PER1-: U1.29 (PER1-), U2.29 (PER1-)
/PER2+: U1.19 (PER2+), U2.19 (PER2+)
/PER2-: U1.17 (PER2-), U2.17 (PER2-)
/PER3+: U1.7 (PER3+), U2.7 (PER3+)
/PER3-: U1.5 (PER3-), U2.5 (PER3-)
/PET0+: U1.49 (PET0+/A+), U2.49 (PET0+/A+)
/PET0-: U1.47 (PET0-/A-), U2.47 (PET0-/A-)
/PET1+: U1.37 (PET1+), U2.37 (PET1+)
/PET1-: U1.35 (PET1-), U2.35 (PET1-)
/PET2+: U1.25 (PET2+), U2.25 (PET2+)
/PET2-: U1.23 (PET2-), U2.23 (PET2-)
/PET3+: U1.13 (PET3+), U2.13 (PET3+)
/PET3-: U1.11 (PET3-), U2.11 (PET3-)
/REFCLK+: U1.55 (REFCLK+), U2.55 (REFCLK+)
/REFCLK-: U1.53 (REFCLK-), U2.53 (REFCLK-)
/SATA_A+: J1.6, U3.49 (PET0+/A+)
/SATA_A-: J1.5, U3.47 (PET0-/A-)
/SATA_B+: J1.2, U3.41 (PER0-/B+)
/SATA_B-: J1.3, U3.43 (PER0+/B-)
DAS+DSS: R5.1, R11.1, U1.10 (DAS/DSS)
DEVSLP: R6.1, R12.1, U1.38 (DEVSLP)
GND: J1.1, J1.4, J1.7, J1.MP (MountPin), R1.2, R2.2, R3.2, R4.2, U1.3 (GND), U1.9 (GND), U1.15 (GND), U1.27 (GND), U1.33 (GND), U1.39 (GND), U1.45 (GND), U1.51 (GND), U1.57 (GND), U1.71 (GND), U1.73 (GND), U1.MP, U2.1 (C3), U2.3 (GND), U2.9 (GND), U2.15 (GND), U2.21 (C0), U2.27 (GND), U2.33 (GND), U2.39 (GND), U2.45 (GND), U2.51 (GND), U2.57 (GND), U2.69 (C1), U2.71 (GND), U2.73 (GND), U2.75 (C2), U2.MP, U3.1 (C3), U3.3 (GND), U3.5 (GND), U3.11 (GND), U3.21 (C0), U3.27 (GND), U3.33 (GND), U3.39 (GND), U3.45 (GND), U3.51 (GND), U3.57 (GND), U3.69 (C1), U3.71 (GND), U3.73 (GND), U3.75 (C2), U3.MP
unnamed: R1.1, U1.1 (C3)
unnamed: R2.1, U1.21 (C0)
unnamed: R3.1, U1.69 (C1)
unnamed: R4.1, U1.75 (C2)
unnamed: R5.2, U2.10 (DAS/DSS)
unnamed: R6.2, U2.38 (DEVSLP)
unnamed: R7.2, U2.50 (~PERST)
unnamed: R8.2, U2.52 (~CLKREQ)
unnamed: R9.2, U2.54 (~PEWAKE)
unnamed: R10.2, U2.68 (SUSCLK)
unnamed: R11.2, U3.10 (DAS/GP9)
unnamed: R12.2, U3.38 (DEVSLP)
unnamed: R13.2, U3.68 (SUSCLK)
SUSCLK: R10.1, R13.1, U1.68 (SUSCLK)
~CLKREQ: R8.1, U1.52 (~CLKREQ)
~PERST: R7.1, U1.50 (~PERST)
~PEWAKE: R9.1, U1.54 (~PEWAKE)
